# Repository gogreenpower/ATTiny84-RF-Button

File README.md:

# ATTiny84-RF-Button
Second PCB design

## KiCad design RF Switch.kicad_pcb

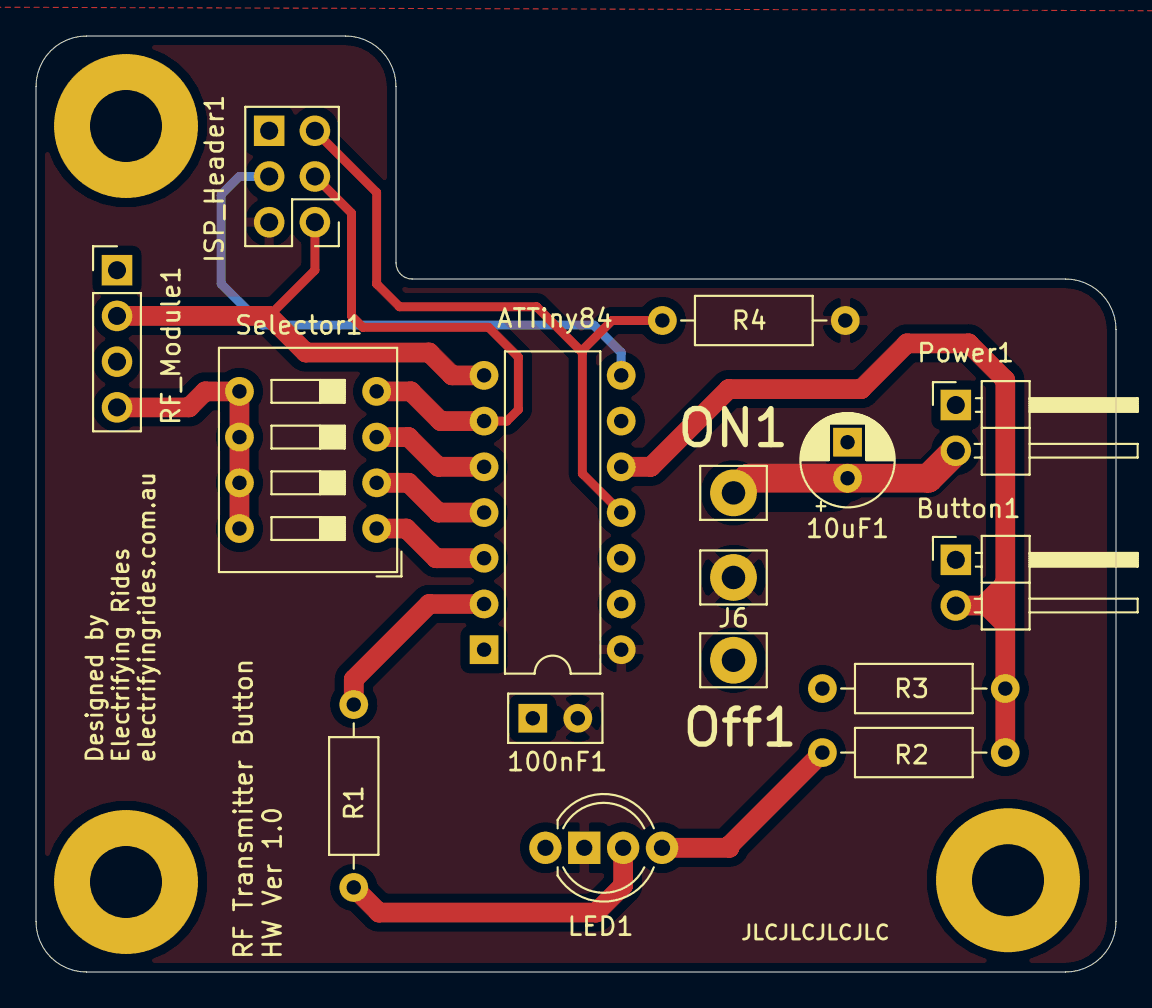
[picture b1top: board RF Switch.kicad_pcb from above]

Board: 2 copper layers, 60.0 x 52.0 mm, 19 parts (0 on the bottom side), 15 nets.

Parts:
10uF1: CP_Radial_D5.0mm_P2.00mm
100nF1: C_Disc_D5.0mm_W2.5mm_P2.50mm
 : MountingHole_2.1mm
 #2,  #3: MountingHole_2.1mm
ATTiny84: ATtiny84-20PU; DIP-14_W7.62mm
Button1: PinHeader_1x02_P2.54mm_Horizontal
ISP_Header1: PinHeader_2x03_P2.54mm_Vertical
J6: On/Off Switch; Pin_D1.3mm_L10.0mm_W3.5mm_Flat
LED1: LED_D5.0mm-4_RGB_Wide_Pins
ON1: Pin_D1.3mm_L10.0mm_W3.5mm_Flat
Off1: Pin_D1.3mm_L10.0mm_W3.5mm_Flat
Power1: PinHeader_1x02_P2.54mm_Horizontal
R1, R2: R220; R_Axial_DIN0207_L6.3mm_D2.5mm_P10.16mm_Horizontal
R3, R4: 10k; R_Axial_DIN0207_L6.3mm_D2.5mm_P10.16mm_Horizontal
RF_Module1: PinHeader_1x04_P2.54mm_Vertical
Selector1: SW_DIP_SPSTx04_Slide_9.78x12.34mm_W7.62mm_P2.54mm

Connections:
+VDC: 100nF1.1, ATTiny84.1, ISP_Header1.2, J6.1, LED1.2, R4.2
GND: 10uF1.2, 100nF1.2, ATTiny84.14, Button1.1, ISP_Header1.6, Power1.1, RF_Module1.1
unnamed: 10uF1.1, ON1.1, Power1.2
unnamed: ATTiny84.4, ISP_Header1.5, R4.1
unnamed: ATTiny84.5, Button1.2, R2.2, R3.1
unnamed: ATTiny84.7, ISP_Header1.4
unnamed: ATTiny84.8, ISP_Header1.1, RF_Module1.2
unnamed: ATTiny84.9, ISP_Header1.3, Selector1.4
unnamed: ATTiny84.10, Selector1.3
unnamed: ATTiny84.11, Selector1.2
unnamed: ATTiny84.12, Selector1.1
unnamed: ATTiny84.13, R1.2
unnamed: LED1.3, R1.1
unnamed: LED1.4, R2.1
unnamed: RF_Module1.4, Selector1.5, Selector1.6, Selector1.7, Selector1.8

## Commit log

2022-02-03 Add files via upload
    added decoupling capacitors C1 and C2, repositioned R1, R2 and R3
2022-02-04 Add files via upload
    Added pull up resistor and C1/C2
2022-02-05 Add files via upload
    componet reposition
2022-02-05 Delete 3d.png
    old version
